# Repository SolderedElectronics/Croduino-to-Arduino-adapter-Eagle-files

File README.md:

# Croduino Croduino to Arduino adapter Eagle Files
## Image

[Croduino to Arduino adapter(100015)](https://e-radionica.com/en/croduino-to-arduino-adapter.html)

## Description and details
If you need to use Arduino shields with the Croduino board, this shield is all you need. Simply plug 'n' play. No need for soldering, connecting jumper wires or using a breadboard. Just directly snap Arduino shield in the adapter and the adapter in Croduino - now everything is connected and ready to use!

## Repository content
This repo contains Cadsoft Eagle .sch and .brd files for Croduino Damba board. It also contains schematic in .pdf created from .sch Eagle file. 
Files have been arranged into folders for navigating between different versions of board. 
Tip: layer 200 shows top silkscreen and layer 208 should be bottom silkscreen. tParts and bParts is not used.

## Docs
- [CAA product page] (https://e-radionica.com/en/croduino-to-arduino-adapter.html)

## Board versions
- v1.0 - inital version

## License info
This product is open-source. Yay!
For any tech questions, contact us at techsupport@e-radionica.com
If you find an Issue, please open one at GitHub. If you can improve our product, fork us.

e-radionica.com Team.

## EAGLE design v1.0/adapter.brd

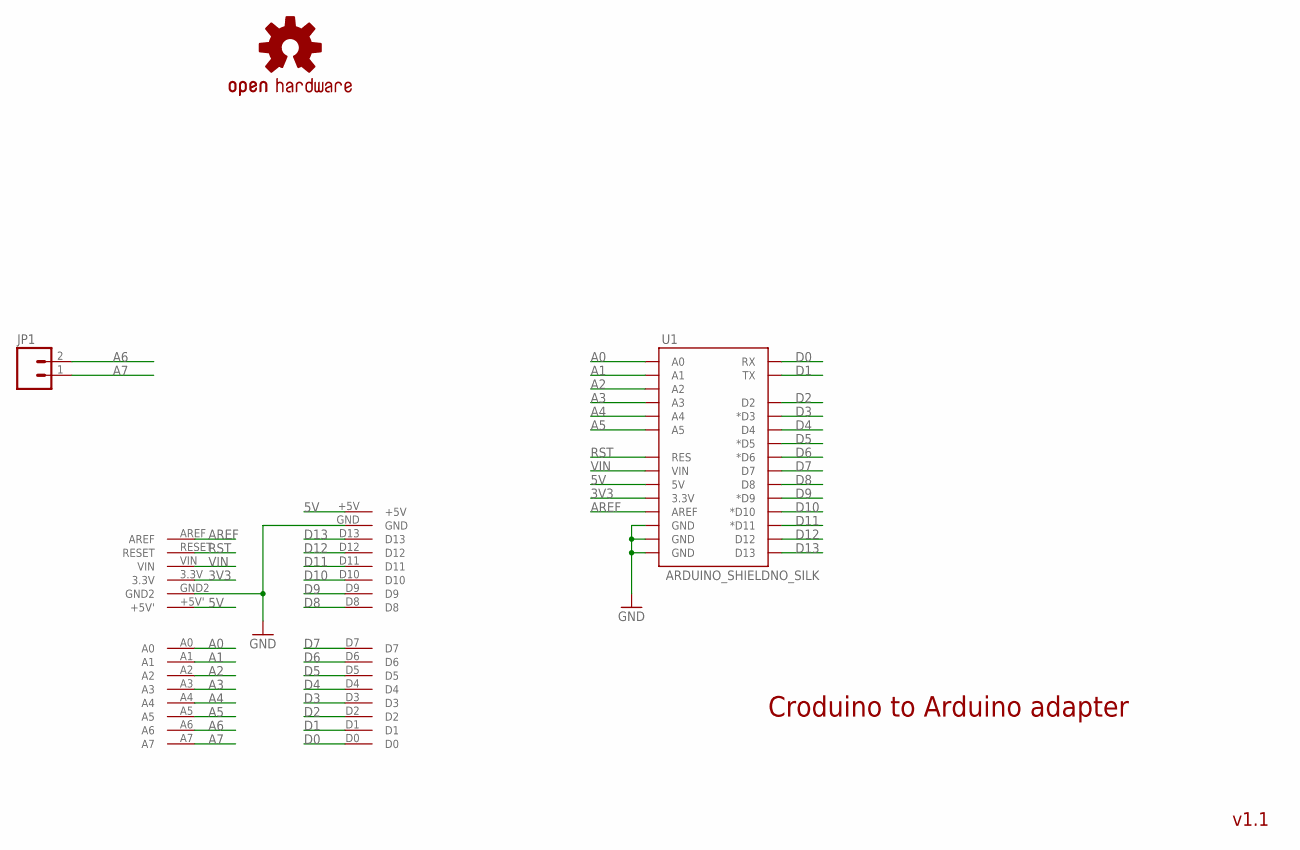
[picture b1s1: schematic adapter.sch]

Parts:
JP1: M02LOCK; 1X02_LOCK
U1: ARDUINO_SHIELDNO_SILK; DUEMILANOVE_VIAS
U$1: CRODUINO_FOOTPRINT
U$4: OSHW-LOGOM; OSHW-LOGO-M

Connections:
3V3: U1.3.3V, U$1.3.3V
5V: U1.5V, U$1.+5V, U$1.+5V'
A0: U1.A0, U$1.A0
A1: U1.A1, U$1.A1
A2: U1.A2, U$1.A2
A3: U1.A3, U$1.A3
A4: U1.A4, U$1.A4
A5: U1.A5, U$1.A5
A6: JP1.2, U$1.A6
A7: JP1.1, U$1.A7
AREF: U1.AREF, U$1.AREF
D0: U1.RX, U$1.D0
D1: U1.TX, U$1.D1
D2: U1.D2, U$1.D2
D3: U1.D3 (*D3), U$1.D3
D4: U1.D4, U$1.D4
D5: U1.D5 (*D5), U$1.D5
D6: U1.D6 (*D6), U$1.D6
D7: U1.D7, U$1.D7
D8: U1.D8, U$1.D8
D9: U1.D9 (*D9), U$1.D9
D10: U1.D10 (*D10), U$1.D10
D11: U1.D11 (*D11), U$1.D11
D12: U1.D12, U$1.D12
D13: U1.D13, U$1.D13
GND: U1.GND@0 (GND), U1.GND@1 (GND), U1.GND@2 (GND), U$1.GND, U$1.GND2
RST: U1.RES, U$1.RESET
VIN: U1.VIN, U$1.VIN

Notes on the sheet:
Croduino to Arduino adapter
v1.1

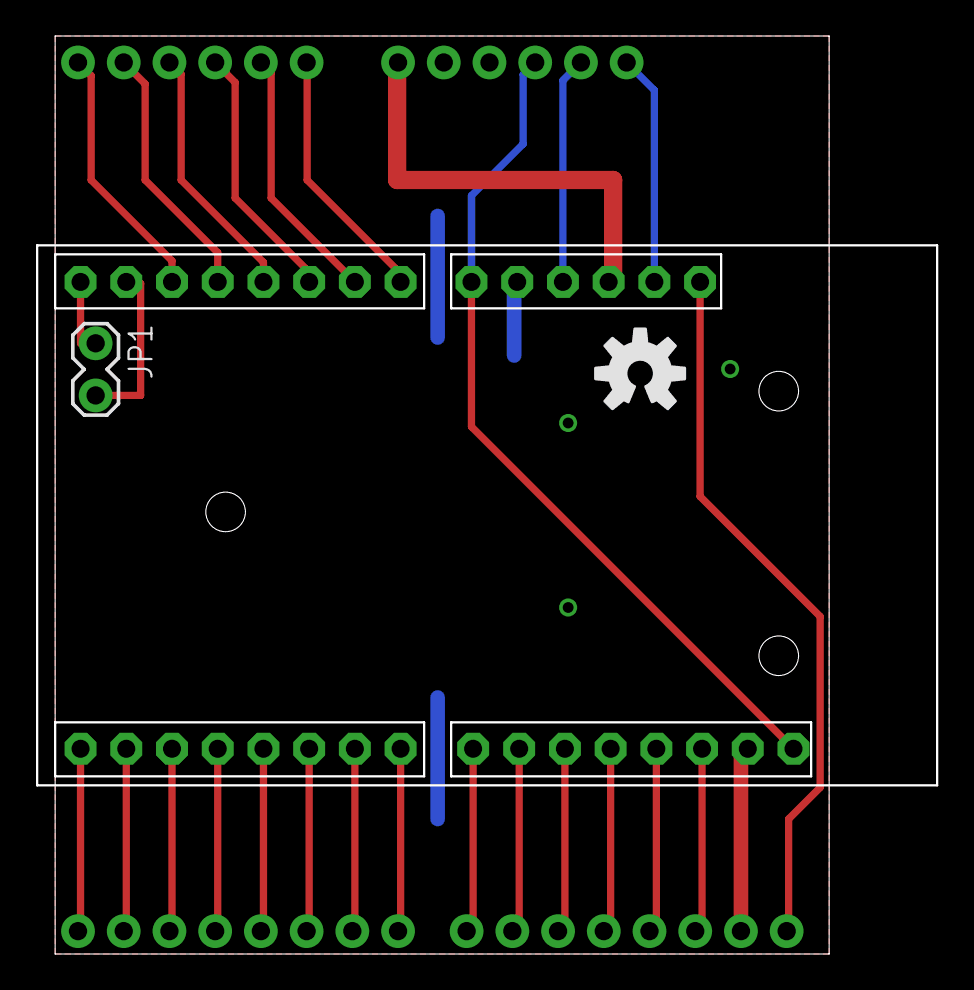
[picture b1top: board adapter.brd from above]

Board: 2 copper layers, 50.0 x 50.9 mm, 7 parts (0 on the bottom side), 28 nets.

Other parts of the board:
U$2: UTICNICA3MM
U$3: MADE-IN-CROATIA
U$5: OSH3MM

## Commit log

2015-08-14 Add files
2015-08-24 Write Readme, add version folder
2016-02-12 README change
    Changed links on e-radionica.com from HTTP to HTTPS since we enabled
    SSL.
2018-11-26 README update

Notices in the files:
parts and their libraries:
SparkFun: Licensing: CC v3.0 Share-Alike You are welcome to use this library for commercial purposes.
